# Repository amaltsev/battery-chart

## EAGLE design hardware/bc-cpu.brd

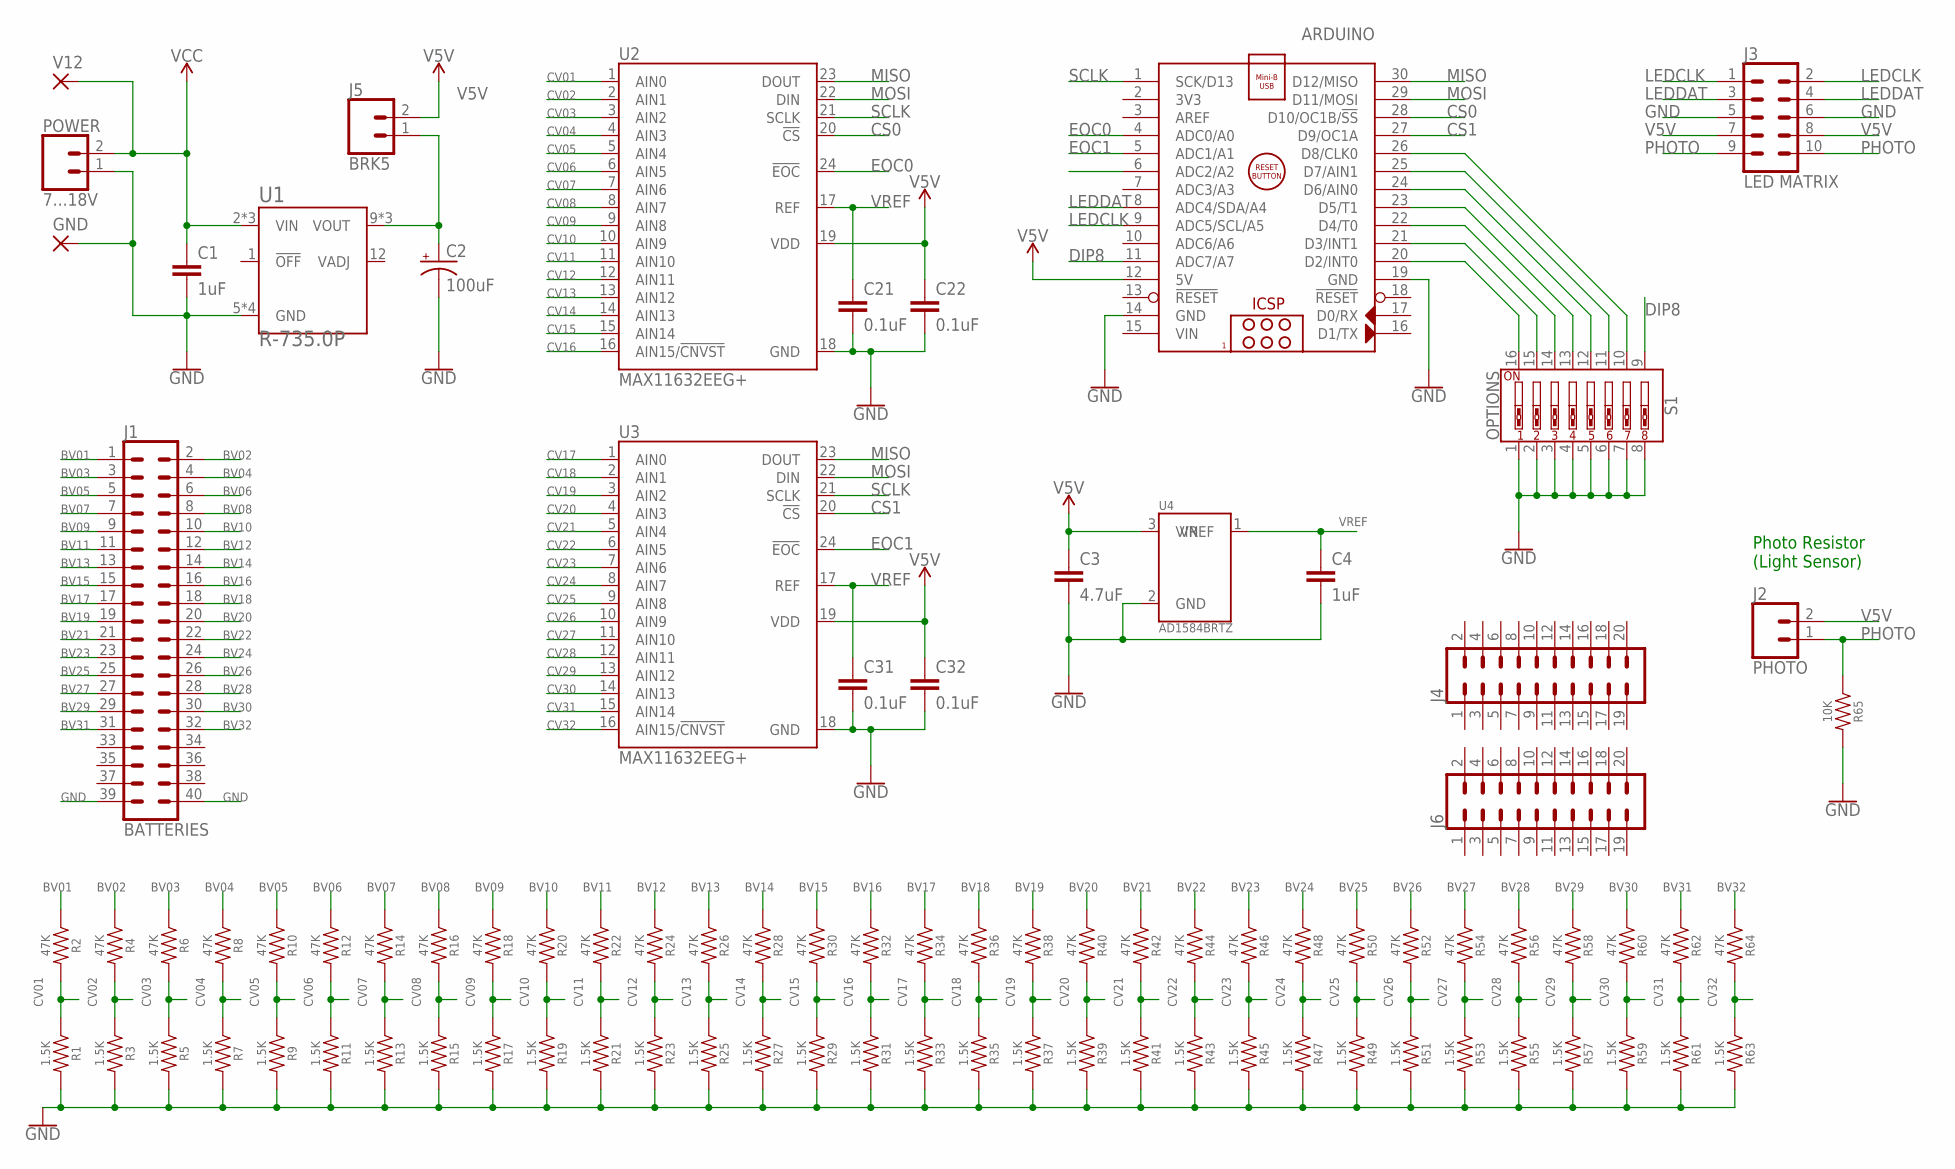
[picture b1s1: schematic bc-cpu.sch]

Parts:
ARDUINO: ARDUINO_NANO
C1, C4: 1uF; C5B3
C2: 100uF; CPOL-RADIAL-2.5MM-6.5MM
C3: 4.7uF; C5B3
C21, C22, C31, C32: 0.1uF; C5B3
GND: WIREPAD3,17/1,2; 3,17/1,2
J1: BATTERIES; 2X20_SHROUDED
J2: PHOTO; 1X02
J3: LED MATRIX; 2X5-SHROUDED
J4, J6: CONN_10X2NOSILK; 2X10_NOSILK
J5: BRK5; 1X02
POWER: 7...18V; 1X02
R1, R3, R5, R7, R9, R11, R13, R15, R17, R19, R21, R23, R25, R27, R29, R31, R33, R35, R37, R39, R41, R43, R45, R47, R49, R51, R53, R55, R57, R59, R61, R63: 1.5K; 1206
R2, R4, R6, R8, R10, R12, R14, R16, R18, R20, R22, R24, R26, R28, R30, R32, R34, R36, R38, R40, R42, R44, R46, R48, R50, R52, R54, R56, R58, R60, R62, R64: 47K; 1206
R65: 10K; AXIAL-0.3
S1: OPTIONS; DIPSWITCH-08
U1: R-735.0P; RECOM-R-7XX.XX
U2, U3: MAX11632EEG+; QSOP24
U4: AD1584BRTZ; SOT23-3
V12: WIREPAD3,17/1,2; 3,17/1,2

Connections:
BV01: J1.1, R2.1
BV02: J1.2, R4.1
BV03: J1.3, R6.1
BV04: J1.4, R8.1
BV05: J1.5, R10.1
BV06: J1.6, R12.1
BV07: J1.7, R14.1
BV08: J1.8, R16.1
BV09: J1.9, R18.1
BV10: J1.10, R20.1
BV11: J1.11, R22.1
BV12: J1.12, R24.1
BV13: J1.13, R26.1
BV14: J1.14, R28.1
BV15: J1.15, R30.1
BV16: J1.16, R32.1
BV17: J1.17, R34.1
BV18: J1.18, R36.1
BV19: J1.19, R38.1
BV20: J1.20, R40.1
BV21: J1.21, R42.1
BV22: J1.22, R44.1
BV23: J1.23, R46.1
BV24: J1.24, R48.1
BV25: J1.25, R50.1
BV26: J1.26, R52.1
BV27: J1.27, R54.1
BV28: J1.28, R56.1
BV29: J1.29, R58.1
BV30: J1.30, R60.1
BV31: J1.31, R62.1
BV32: J1.32, R64.1
CS0: ARDUINO.28 (D10/OC1B/!SS), U2.20 (!CS)
CS1: ARDUINO.27 (D9/OC1A), U3.20 (!CS)
CV01: R1.1, R2.2, U2.1 (AIN0)
CV02: R3.1, R4.2, U2.2 (AIN1)
CV03: R5.1, R6.2, U2.3 (AIN2)
CV04: R7.1, R8.2, U2.4 (AIN3)
CV05: R9.1, R10.2, U2.5 (AIN4)
CV06: R11.1, R12.2, U2.6 (AIN5)
CV07: R13.1, R14.2, U2.7 (AIN6)
CV08: R15.1, R16.2, U2.8 (AIN7)
CV09: R17.1, R18.2, U2.9 (AIN8)
CV10: R19.1, R20.2, U2.10 (AIN9)
CV11: R21.1, R22.2, U2.11 (AIN10)
CV12: R23.1, R24.2, U2.12 (AIN11)
CV13: R25.1, R26.2, U2.13 (AIN12)
CV14: R27.1, R28.2, U2.14 (AIN13)
CV15: R29.1, R30.2, U2.15 (AIN14)
CV16: R31.1, R32.2, U2.16 (AIN15/!CNVST)
CV17: R33.1, R34.2, U3.1 (AIN0)
CV18: R35.1, R36.2, U3.2 (AIN1)
CV19: R37.1, R38.2, U3.3 (AIN2)
CV20: R39.1, R40.2, U3.4 (AIN3)
CV21: R41.1, R42.2, U3.5 (AIN4)
CV22: R43.1, R44.2, U3.6 (AIN5)
CV23: R45.1, R46.2, U3.7 (AIN6)
CV24: R47.1, R48.2, U3.8 (AIN7)
CV25: R49.1, R50.2, U3.9 (AIN8)
CV26: R51.1, R52.2, U3.10 (AIN9)
CV27: R53.1, R54.2, U3.11 (AIN10)
CV28: R55.1, R56.2, U3.12 (AIN11)
CV29: R57.1, R58.2, U3.13 (AIN12)
CV30: R59.1, R60.2, U3.14 (AIN13)
CV31: R61.1, R62.2, U3.15 (AIN14)
CV32: R63.1, R64.2, U3.16 (AIN15/!CNVST)
DIP1: ARDUINO.20 (D2/INT0), S1.16
DIP2: ARDUINO.21 (D3/INT1), S1.15
DIP3: ARDUINO.22 (D4/T0), S1.14
DIP4: ARDUINO.23 (D5/T1), S1.13
DIP5: ARDUINO.24 (D6/AIN0), S1.12
DIP6: ARDUINO.25 (D7/AIN1), S1.11
DIP7: ARDUINO.26 (D8/CLK0), S1.10
DIP8: ARDUINO.11 (ADC7/A7), S1.9
EOC0: ARDUINO.4 (ADC0/A0), U2.24 (!EOC)
EOC1: ARDUINO.5 (ADC1/A1), U3.24 (!EOC)
GND: ARDUINO.14 (GND), ARDUINO.19 (GND), C1.2, C2.2 (-), C3.2, C4.2, C21.2, C22.2, C31.2, C32.2, GND.1, J1.39, J1.40, J3.5, J3.6, POWER.1, R1.2, R3.2, R5.2, R7.2, R9.2, R11.2, R13.2, R15.2, R17.2, R19.2, R21.2, R23.2, R25.2, R27.2, R29.2, R31.2, R33.2, R35.2, R37.2, R39.2, R41.2, R43.2, R45.2, R47.2, R49.2, R51.2, R53.2, R55.2, R57.2, R59.2, R61.2, R63.2, R65.P$2 (2), S1.1, S1.2, S1.3, S1.4, S1.5, S1.6, S1.7, S1.8, U1.5 (GND), U1.6 (GND), U1.7 (GND), U1.8 (GND), U2.18 (GND), U3.18 (GND), U4.2 (GND)
LEDCLK: ARDUINO.9 (ADC5/SCL/A5), J3.1, J3.2
LEDDAT: ARDUINO.8 (ADC4/SDA/A4), J3.3, J3.4
MISO: ARDUINO.30 (D12/MISO), U2.23 (DOUT), U3.23 (DOUT)
MOSI: ARDUINO.29 (D11/MOSI), U2.22 (DIN), U3.22 (DIN)
unnamed: C2.1 (+), J5.1, U1.9 (VOUT), U1.10 (VOUT), U1.11 (VOUT)
PHOTO: ARDUINO.6 (ADC2/A2), J2.1, J3.9, J3.10, R65.P$1 (1)
SCLK: ARDUINO.1 (SCK/D13), U2.21 (SCLK), U3.21 (SCLK)
V5V: ARDUINO.12 (5V), C3.1, C22.1, C32.1, J2.2, J3.7, J3.8, J5.2, U2.19 (VDD), U3.19 (VDD), U4.3 (VIN)
VCC: C1.1, POWER.2, U1.2 (VIN), U1.3 (VIN), U1.4 (VIN), V12.1
VIN: ARDUINO.15 (VIN)
VREF: C4.1, C21.1, C31.1, U2.17 (REF), U3.17 (REF), U4.1 (VREF)

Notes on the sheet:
Photo Resistor (Light Sensor)

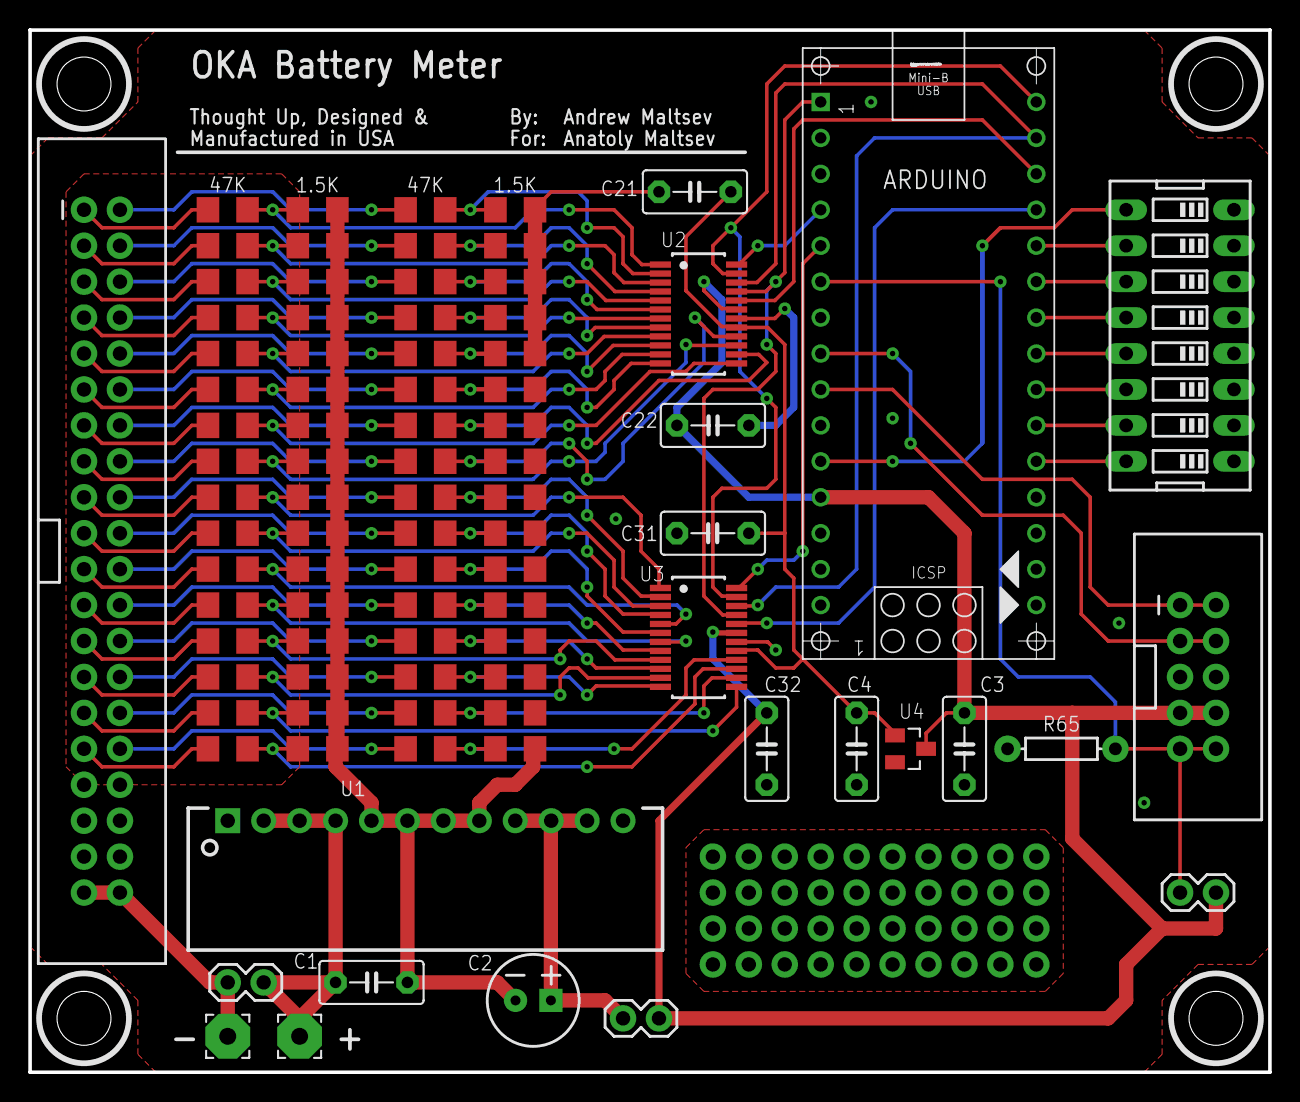
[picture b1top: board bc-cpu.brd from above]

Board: 2 copper layers, 87.6 x 73.7 mm, 88 parts (0 on the bottom side), 87 nets.

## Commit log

2017-05-08 Initial commit
    Incomplete schematic, just building library parts and starting...
2017-05-08 Added resistors array
2017-05-08 Added voltage reference
2017-05-09 Final schematic, before PCB
2017-05-09 The initial rats nest
2017-05-09 Rough placement, no routes
2017-05-10 Layout attempt with SMD MAX-11632
    Lots of random traces that need to be placed by hand. Committing before
    trying a different approach.
2017-05-10 More organized routing
    This starts to look like it might work... :)
2017-05-10 ADC 1 mostly routed
2017-05-10 Fixed VREF bug, mostly routed
2017-05-11 All routed, DRC checks passing
    Also removed drill holes from Arduino Nano lib -- they were translating
    into the board for no reason. Replaced them with just silkscreen.
2017-05-11 Text, labels, positioning
2017-05-11 Power input adjustments
2017-05-11 Changed font to vector
2017-05-11 Extra air gap around inputs
    120V is not going to bridge even 1mil, but removed copper pour around
    terminals just in case anyway.
2017-05-11 Gerber output - off to Fabrication
2017-05-21 Final board, as ordered from OSHPark
2017-05-28 Multi-matrix controls
    Works in all orientations as a single 32x16 display over the GFX
    library.
2017-05-29 Added voltage reader, calibrated
    Readings are VERY consistent. I expected accuracy, but not actually at
    that level, where values are exactly identical over all 32 channels and
    over hundreds of measures.
2017-05-29 Fixed calibration typo and recalibrated
    Still consistent enough, to within 1/153rd of the value after division,
    or about 32mV in the source value -- below what can be displayed.
2017-05-29 Actual voltage measuring and conversion
    Works great in initial tests. Allows for connecting input in any order,
    compensates for broken connections.
2017-05-30 DIP Switch Options
2017-05-30 Voltage chart works!
    Supports options: rotation, fill, draw bottom. Displays banks and total
    on the far right if there is space for it.
2017-05-30 Demo/Test mode added
    Controlled with DIP Switch 1.
2017-05-30 Added blinking bottom pixes when low voltage
2017-05-30 Better warning blinking
2017-05-30 Added an animated greeting
    Still need to make a nice bitmap for it.
2017-05-30 Hysteresis attempt, not a good one
    Tried to add a bit of hysteresis to avoid pixel blinking at borderline
    values. Did that at voltage input level, which is probably too precise.
    Move it to display at pixel level?
2017-05-31 "OKA ELECTRO" bitmap
2017-05-31 Greeting final changes
2017-05-31 A better and simpler hysteresis implementation
    Just math, no buffer. Having different cut-off fractions depending on
    the current state of the column -- essentially resisisting changes.
2017-06-01 Fixed display bug with live disconnects
    It did not clear measured values when some were disconnected during run
    time.
2017-06-01 Ambient brightness sensor and reaction
    Fixed the hardware -- forgot to wire the photosensor :(
    Added display brightness adjustment to the ambient light, with a 10
    second averaging.

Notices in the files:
parts and their libraries:
SparkFun-Capacitors: Licensing: Creative Commons ShareAlike 4.0 International - https://creativecommons.org/licenses/by-sa/4.0
